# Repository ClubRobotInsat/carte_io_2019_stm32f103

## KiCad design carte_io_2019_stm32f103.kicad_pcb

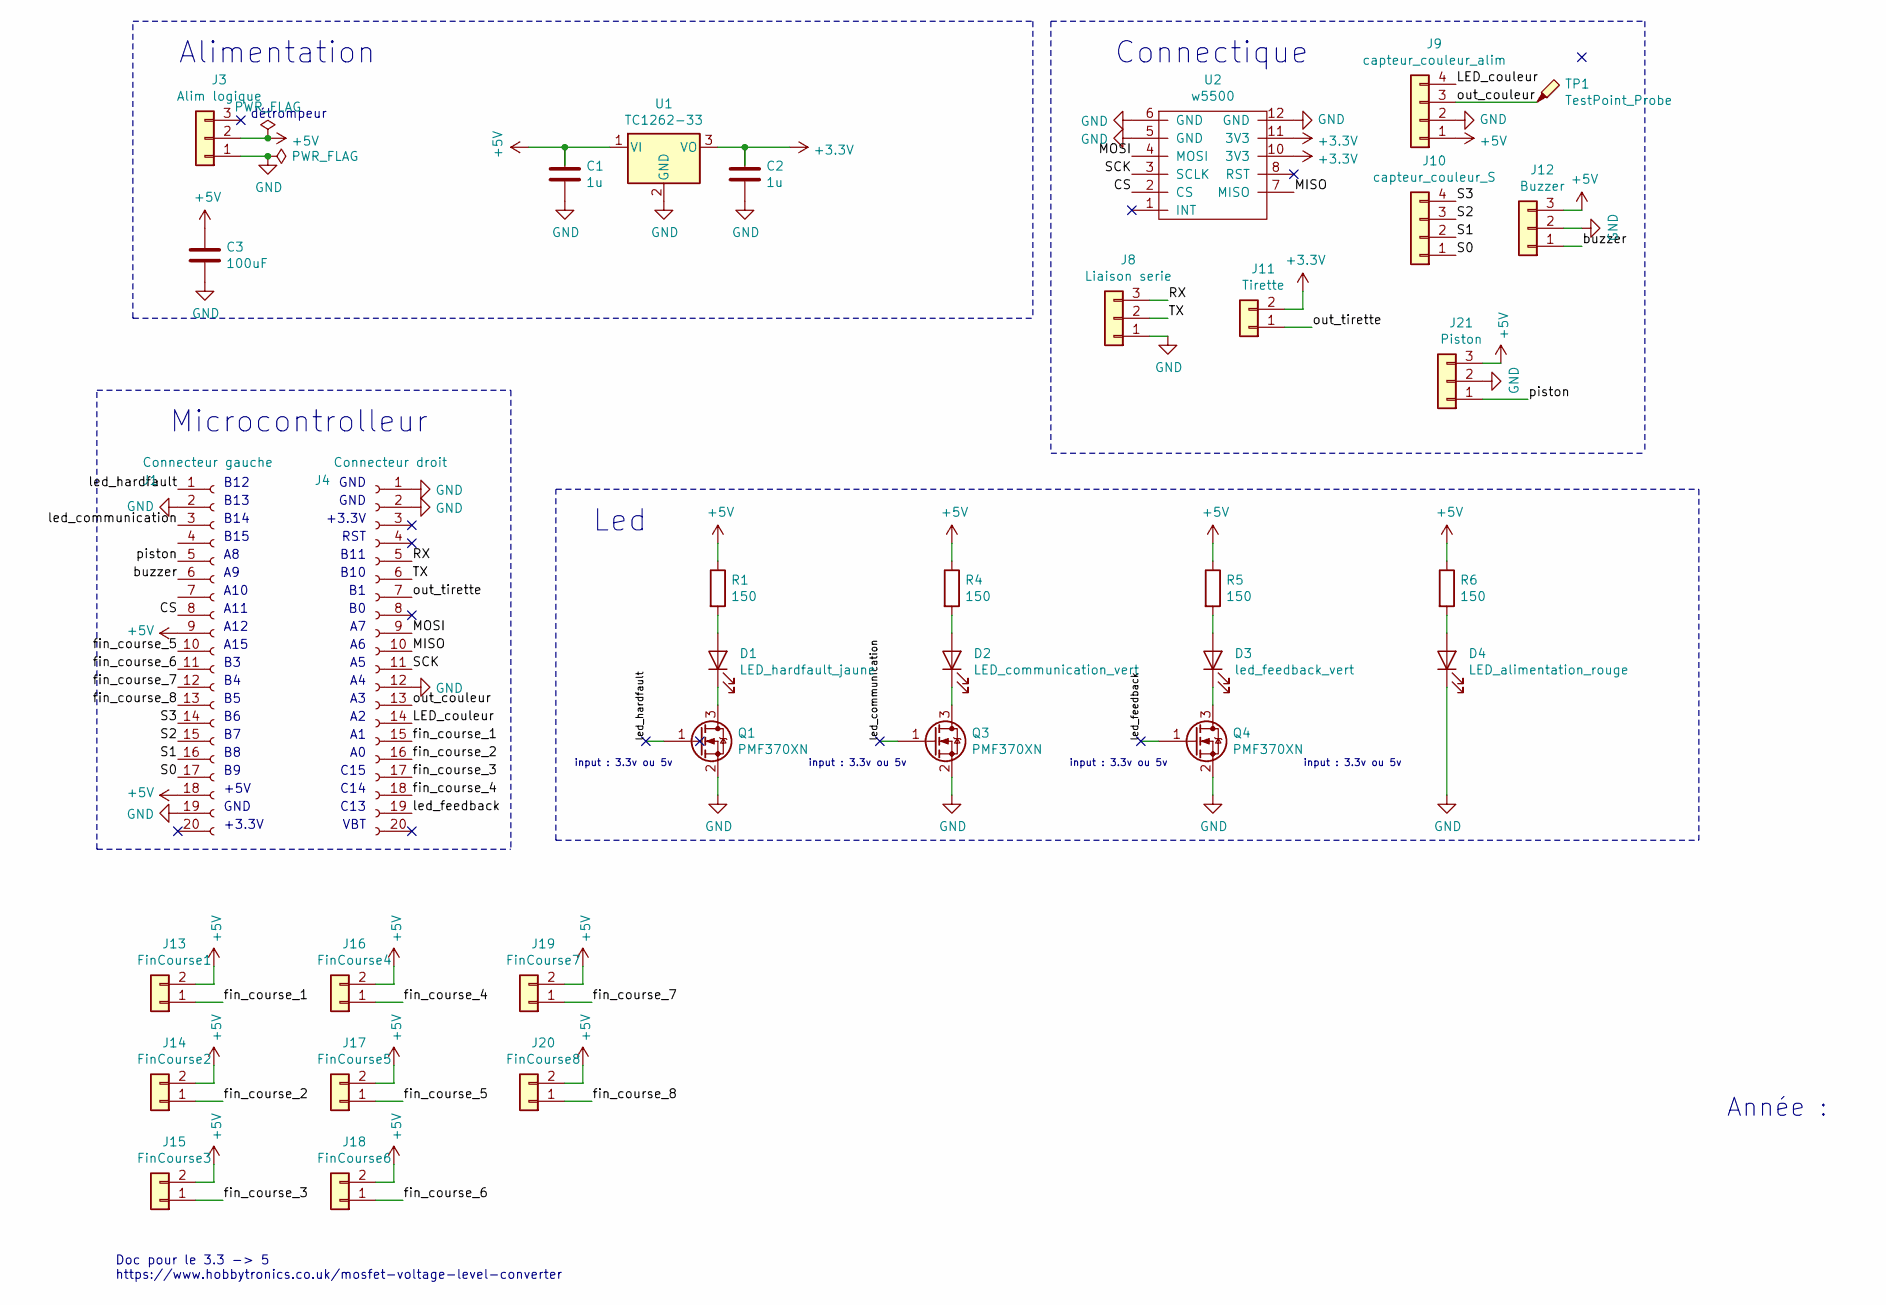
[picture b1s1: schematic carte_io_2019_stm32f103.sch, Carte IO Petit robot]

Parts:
C1, C2: 1u; C_1206_3216Metric_Pad1.42x1.75mm_HandSolder
C3: 100uF; CP_Radial_D6.3mm_P2.50mm
D1: LED_hardfault_jaune; LED_D3.0mm
D2: LED_communication_vert; LED_D3.0mm
D3: led_feedback_vert; LED_D3.0mm
D4: LED_alimentation_rouge; LED_D3.0mm
J1: Connecteur gauche; PinSocket_1x20_P2.54mm_Vertical_Long_Pads
J3: Alim logique; TerminalBlock_Phoenix_MPT-0,5-3-2.54_1x03_P2.54mm_Horizontal
J4: Connecteur droit; PinSocket_1x20_P2.54mm_Vertical_Long_Pads
J8: Liaison serie; TerminalBlock_Phoenix_MPT-0,5-3-2.54_1x03_P2.54mm_Horizontal
J9: capteur_couleur_alim; TerminalBlock_Phoenix_MPT-0,5-4-2.54_1x04_P2.54mm_Horizontal
J10: capteur_couleur_S; TerminalBlock_Phoenix_MPT-0,5-4-2.54_1x04_P2.54mm_Horizontal
J11: Tirette; TerminalBlock_Phoenix_MPT-0,5-2-2.54_1x02_P2.54mm_Horizontal
J12: Buzzer; HE14-3-straight
J13: FinCourse1; TerminalBlock_Phoenix_MPT-0,5-2-2.54_1x02_P2.54mm_Horizontal
J14: FinCourse2; TerminalBlock_Phoenix_MPT-0,5-2-2.54_1x02_P2.54mm_Horizontal
J15: FinCourse3; TerminalBlock_Phoenix_MPT-0,5-2-2.54_1x02_P2.54mm_Horizontal
J16: FinCourse4; TerminalBlock_Phoenix_MPT-0,5-2-2.54_1x02_P2.54mm_Horizontal
J17: FinCourse5; TerminalBlock_Phoenix_MPT-0,5-2-2.54_1x02_P2.54mm_Horizontal
J18: FinCourse6; TerminalBlock_Phoenix_MPT-0,5-2-2.54_1x02_P2.54mm_Horizontal
J19: FinCourse7; TerminalBlock_Phoenix_MPT-0,5-2-2.54_1x02_P2.54mm_Horizontal
J20: FinCourse8; TerminalBlock_Phoenix_MPT-0,5-2-2.54_1x02_P2.54mm_Horizontal
J21: Piston; TerminalBlock_Phoenix_MPT-0,5-3-2.54_1x03_P2.54mm_Horizontal
Q1, Q3, Q4: PMF370XN; SOT-323_SC-70_Handsoldering
R1, R4, R5, R6: 150; R_1206_3216Metric_Pad1.42x1.75mm_HandSolder
TP1: TestPoint_Probe; PinHeader_1x01_P1.00mm_Vertical
U1: TC1262-33; SOT-223-3_TabPin2
U2: w5500

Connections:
+3V3: C2.1, J11.2, U1.3 (VO), U2.10 (3V3), U2.11 (3V3)
+5V: C1.1, C3.1, J1.9, J1.18, J3.2, J9.1, J12.3, J13.2, J14.2, J15.2, J16.2, J17.2, J18.2, J19.2, J20.2, J21.3, R1.1, R4.1, R5.1, R6.1, U1.1 (VI)
/CS: J1.8, U2.2 (CS)
/LED_couleur: J4.14, J9.4
/MISO: J4.10, U2.7 (MISO)
/MOSI: J4.9, U2.4 (MOSI)
/RX: J4.5, J8.3
/S0: J1.17, J10.1
/S1: J1.16, J10.2
/S2: J1.15, J10.3
/S3: J1.14, J10.4
/SCK: J4.11, U2.3 (SCLK)
/TX: J4.6, J8.2
/buzzer: J1.6, J12.1
/fin_course_1: J4.15, J13.1
/fin_course_2: J4.16, J14.1
/fin_course_3: J4.17, J15.1
/fin_course_4: J4.18, J16.1
/fin_course_5: J1.10, J17.1
/fin_course_6: J1.11, J18.1
/fin_course_7: J1.12, J19.1
/fin_course_8: J1.13, J20.1
/led_communication: J1.3, Q3.1 (G)
/led_feedback: J4.19, Q4.1 (G)
/led_hardfault: J1.1, Q1.1 (G)
/out_couleur: J4.13, J9.3, TP1.1
/out_tirette: J4.7, J11.1
/piston: J1.5, J21.1
GND: C1.2, C2.2, C3.2, D4.1 (K), J1.2, J1.19, J3.1, J4.1, J4.2, J4.12, J8.1, J9.2, J12.2, J21.2, Q1.2 (S), Q3.2 (S), Q4.2 (S), U1.2 (GND), U2.5 (GND), U2.6 (GND), U2.12 (GND)
unnamed: D1.1 (K), Q1.3 (D)
unnamed: D1.2 (A), R1.2
unnamed: D2.1 (K), Q3.3 (D)
unnamed: D2.2 (A), R4.2
unnamed: D3.1 (K), Q4.3 (D)
unnamed: D3.2 (A), R5.2
unnamed: D4.2 (A), R6.2

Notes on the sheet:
Alimentation
Led
input : 3.3v ou 5v
Microcontrolleur
Connectique
détrompeur
Doc pour le 3.3 -> 5 https://www.hobbytronics.co.uk/mosfet-voltage-level-converter
VBT
C13
C14
C15
B10
B11
RST
+3.3V
GND
+5V
A15
A12
A11
A10
B15
B14
B13
B12
Année :

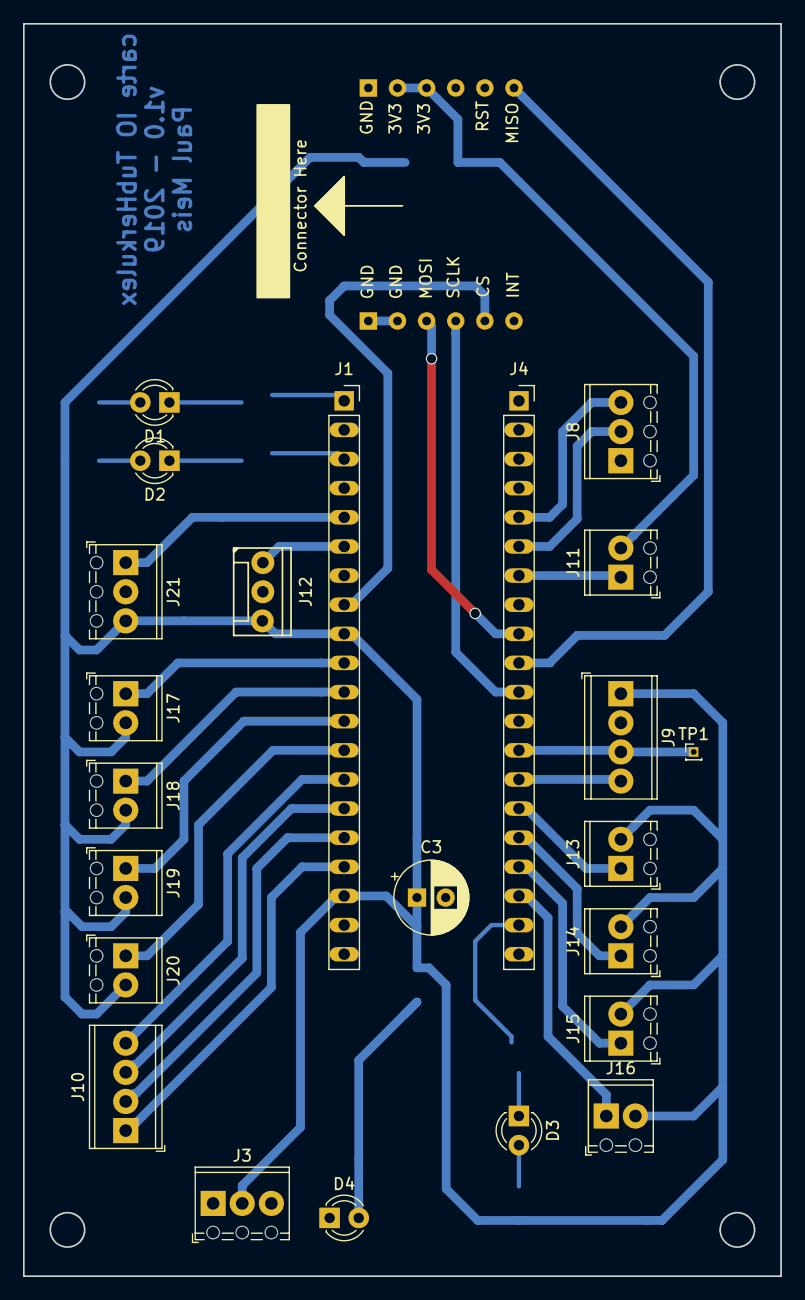
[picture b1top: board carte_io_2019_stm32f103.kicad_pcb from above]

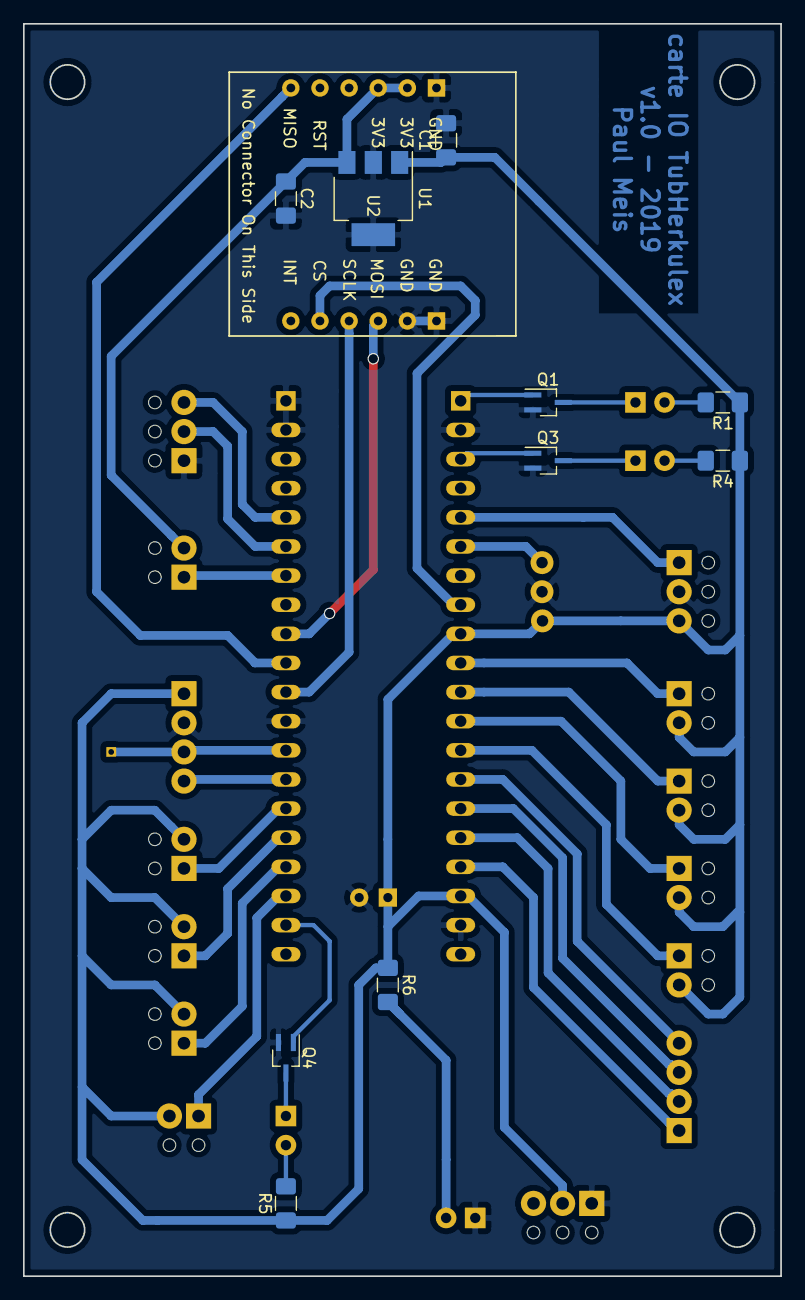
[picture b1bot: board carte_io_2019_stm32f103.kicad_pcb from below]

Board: 2 copper layers, 66.0 x 109.2 mm, 34 parts (10 on the bottom side), 36 nets.

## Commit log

2019-05-02 Version finale (peut être pas utile on verra)
2019-05-16 Ajout des capteurs de fin de course
2019-05-16 Fix buzzer
2019-05-17 Replacage de led_feedback sur PC13
2019-05-17 Add metadata to schematic and PCB
